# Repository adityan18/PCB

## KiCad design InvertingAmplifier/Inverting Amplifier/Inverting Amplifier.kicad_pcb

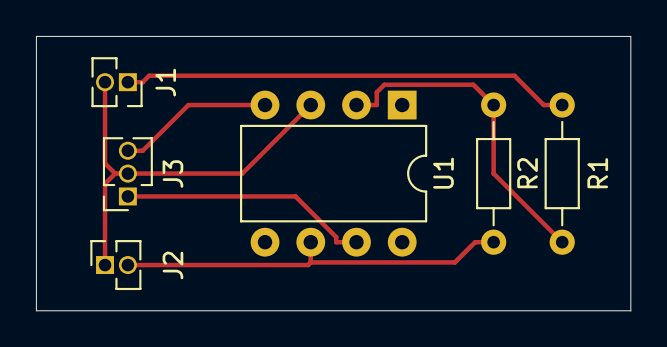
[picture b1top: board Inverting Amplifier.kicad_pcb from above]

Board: 2 copper layers, 33.0 x 15.2 mm, 6 parts (0 on the bottom side), 6 nets.

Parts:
J1: Vin; PinSocket_1x02_P1.27mm_Vertical
J2: Vo; PinSocket_1x02_P1.27mm_Vertical
J3: Power; PinSocket_1x03_P1.27mm_Vertical
R1: 1k; R_Axial_DIN0204_L3.6mm_D1.6mm_P7.62mm_Horizontal
R2: 10k; R_Axial_DIN0204_L3.6mm_D1.6mm_P7.62mm_Horizontal
U1: LM741; DIP-8_W7.62mm

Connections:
+12V: J3.1, U1.7
-12V: J3.3, U1.4
GND: J1.2, J2.1, J3.2, U1.3
unnamed: J1.1, R1.2
unnamed: J2.2, R2.2, U1.6
unnamed: R1.1, R2.1, U1.2

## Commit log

2020-06-06 InvertingAmplifier
2020-06-06 Edge Cut
2020-06-06 Gerber
